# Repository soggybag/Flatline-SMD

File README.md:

# Flatline+ (1590B)

An optical compressor for guitar, built on John Hollis's Flatline with Atomium Amps' mods and your OPA2134 build (super-freq.com/flatline-op2134). Added:
- BLEND (parallel compression);
- a gain-reduction LED;
- a RELEASE switch;
- a side chain buffered off the audio path.

SMD parts are assembled by JLCPCB; the panel parts are hand-soldered on the back.

## Controls

| Control | Part | What it does |
|---|---|---|
| SUSTAIN | RV1 A100k | Gain into the optical gain cell (×3 to ×23): more sustain, more squash |
| BLEND | RV3 B100k | Dry ↔ compressed |
| VOLUME | RV4 A100k | Output level |
| RELEASE | SW1 sub-mini SPDT | FAST 220 µF (stock) / SLOW 440 µF |
| GR LED | D6 | Glows as hard as it's compressing |
| ON LED | D7 | Lit by the footswitch (LED_K) |
| Trim | RV2 3362P 1k | LED-string current (the original POT1) |

## Board

- **Outline and drilling:** the Trem v2 board outline (45 × 50 mm) and its 1590B panel grid.
  - Top row: SUSTAIN · GR LED · VOLUME.
  - Middle: RELEASE · BLEND · ON LED.
  - Bottom: footswitch.
- **Wiring:** a 1×4 header (IN / LED / GND / OUT) runs straight to SwitchPCB v2. There are 9V/GND pads, and IN GND / OUT GND pads for the jack sleeves.
- **Op-amps:** U1 OPA2134UA (LCSC C87361, extended) for audio; U2 TL072 (C6961) for the side chain.
- **Vactrol (U3):** Xvive VTL5C3, or a DIY LED + LDR in heat-shrink. It stands vertically between RELEASE and BLEND.
- **Release caps:** C8/C9 are 220 µF DMBJ (C970695), with `FT Rotation Offset 180` so JLC places them the right way round.

Design notes: [docs/Design Notes.md](docs/Design%20Notes.md). Schematic: [docs/Flatline_schematic.pdf](docs/Flatline_schematic.pdf).

## Status

- **2026-10-07:** schematic and board done.
  - ERC 0.
  - DRC 0 errors, 0 unconnected, schematic parity 0. Only silkscreen warnings remain.
  - GND pours on both layers.
- **Next:** your silkscreen pass, then the JLC fab files.

## Files

- `scripts/`:
  - `build_flatline.py`: the schematic;
  - `buildpcb_flatline.py`: placement;
  - `nudge.py`: clears overlaps.

  Don't re-run them after editing the board in KiCad.
- **Routing:** with `_tools/autoroute.py`.

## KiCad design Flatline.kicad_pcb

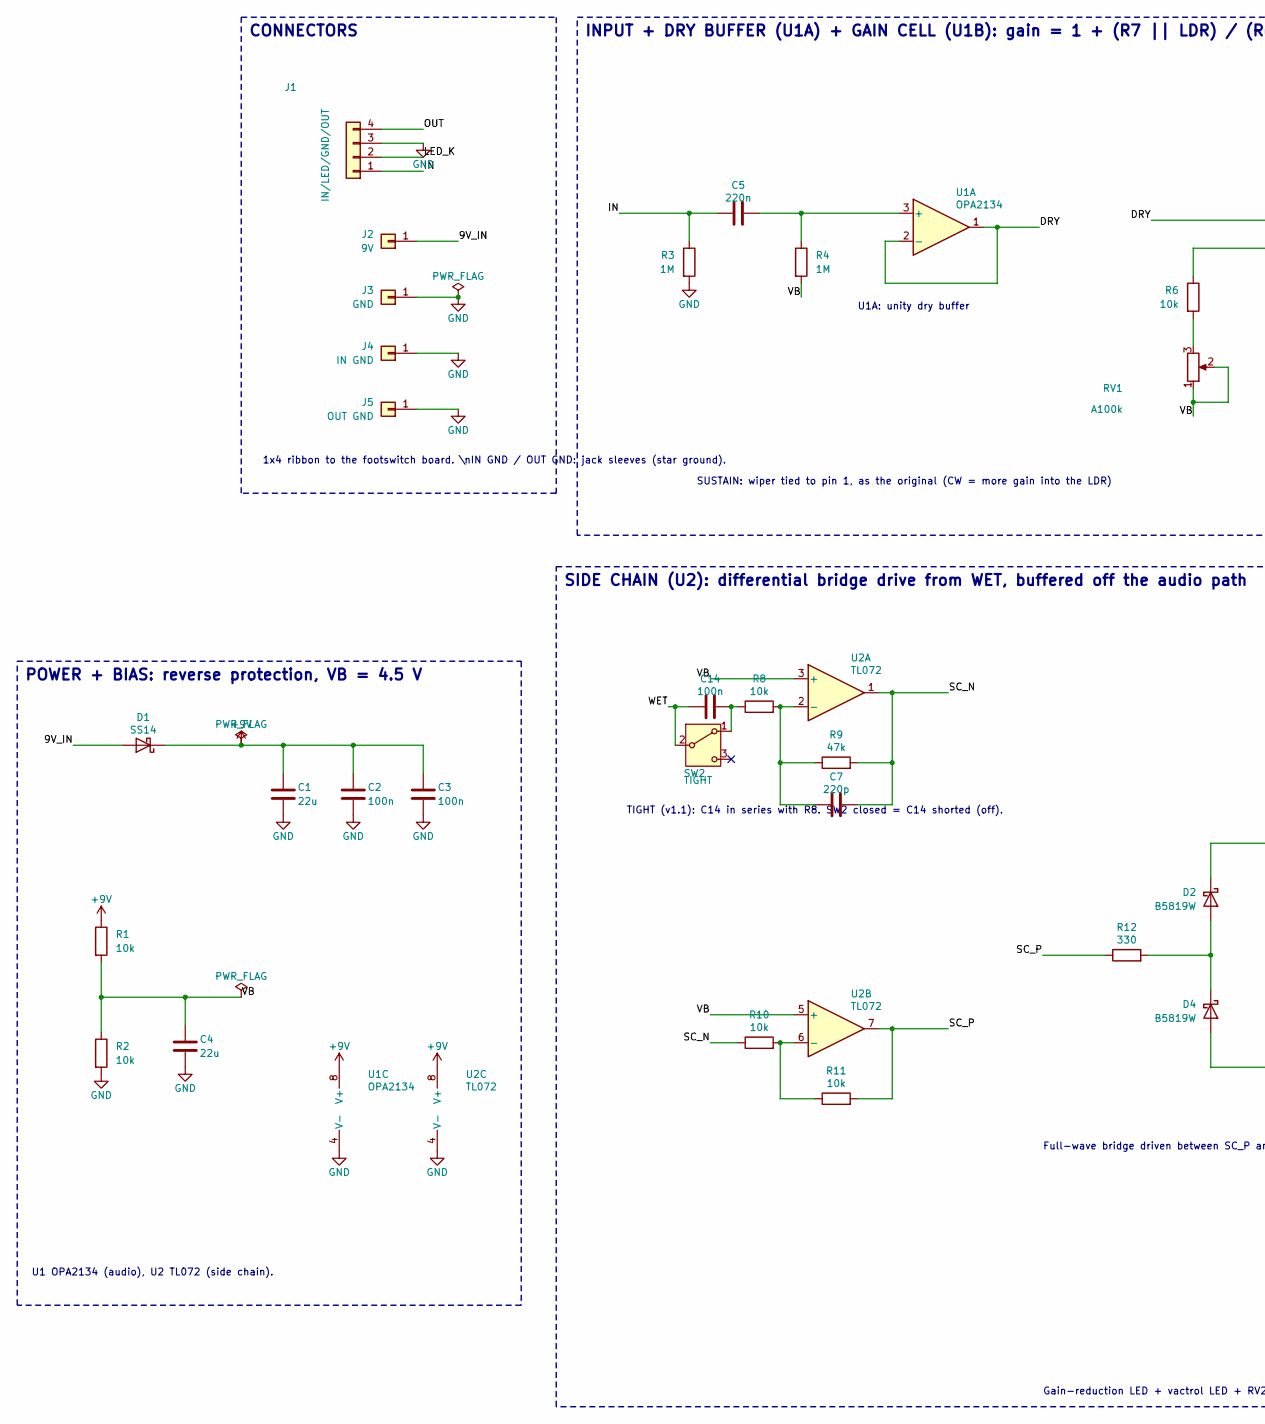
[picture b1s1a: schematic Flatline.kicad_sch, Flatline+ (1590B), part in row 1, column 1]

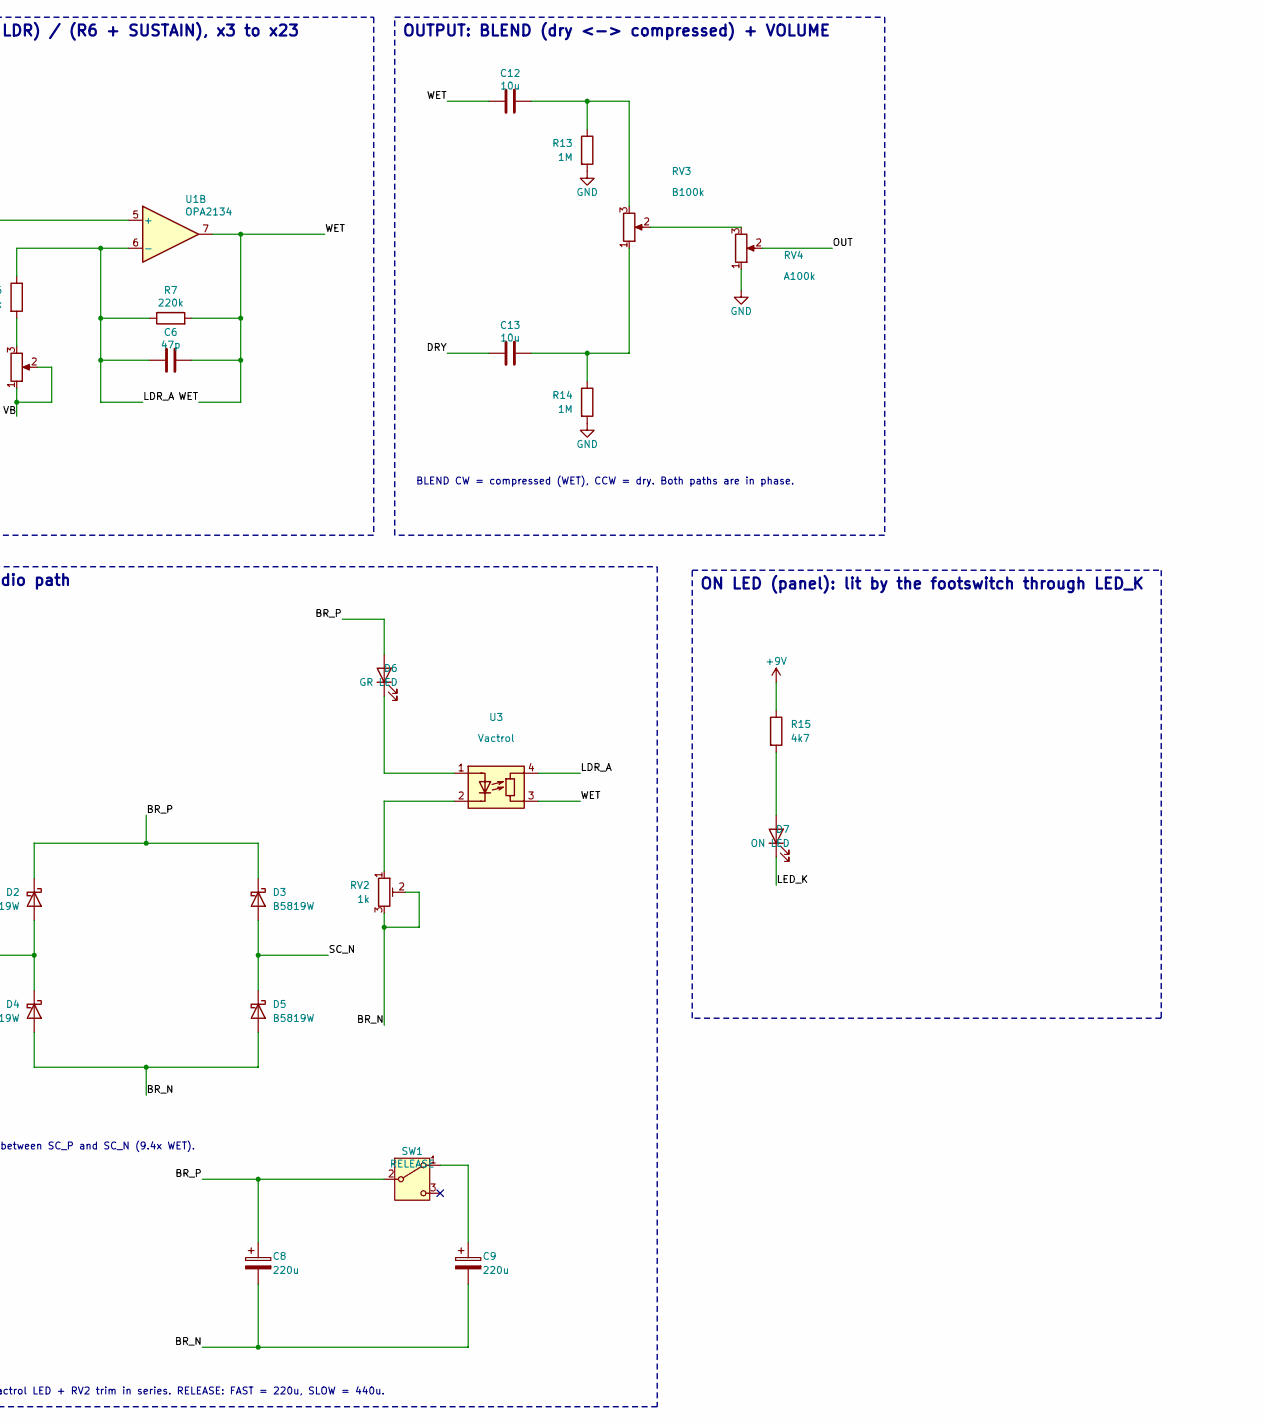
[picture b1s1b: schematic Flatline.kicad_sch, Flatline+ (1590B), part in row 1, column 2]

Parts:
C1, C4: 22u; C_0805_2012Metric_Pad1.18x1.45mm_HandSolder; LCSC C45783
C2, C3, C14: 100n; C_0805_2012Metric_Pad1.18x1.45mm_HandSolder; LCSC C49678
C5: 220n; C_0805_2012Metric_Pad1.18x1.45mm_HandSolder; LCSC C5378
C6: 47p; C_0805_2012Metric_Pad1.18x1.45mm_HandSolder; LCSC C14857
C7: 220p; C_0805_2012Metric_Pad1.18x1.45mm_HandSolder; LCSC C107145
C8, C9: 220u; CP_Elec_6.3x7.7; LCSC C970695
C12, C13: 10u; C_0805_2012Metric_Pad1.18x1.45mm_HandSolder; LCSC C15850
D1: SS14; D_SMA; LCSC C2480
D2, D3, D4, D5: B5819W; D_SOD-123; LCSC C8598
D6: GR LED; LED_D3.0mm
D7: ON LED; LED_D3.0mm
J1: IN/LED/GND/OUT; PinHeader_1x04_P2.54mm_Vertical
J2: 9V; SolderWire-0.5sqmm_1x01_D0.9mm_OD2.1mm
J3: GND; SolderWire-0.5sqmm_1x01_D0.9mm_OD2.1mm
J4: IN GND; SolderWire-0.5sqmm_1x01_D0.9mm_OD2.1mm
J5: OUT GND; SolderWire-0.5sqmm_1x01_D0.9mm_OD2.1mm
R1, R2, R6, R8, R10, R11: 10k; R_0805_2012Metric_Pad1.20x1.40mm_HandSolder; LCSC C17414
R3, R4, R13, R14: 1M; R_0805_2012Metric_Pad1.20x1.40mm_HandSolder; LCSC C17514
R7: 220k; R_0805_2012Metric_Pad1.20x1.40mm_HandSolder; LCSC C17556
R9: 47k; R_0805_2012Metric_Pad1.20x1.40mm_HandSolder; LCSC C17713
R12: 330; R_0805_2012Metric_Pad1.20x1.40mm_HandSolder; LCSC C17630
R15: 4k7; R_0805_2012Metric_Pad1.20x1.40mm_HandSolder; LCSC C17673
RV1, RV4: A100k; Potentiometer_Alpha_RD901F-40-00D_Single_Vertical
RV2: 1k; Potentiometer_Bourns_3362P_Vertical
RV3: B100k; Potentiometer_Alpha_RD901F-40-00D_Single_Vertical
SW1: RELEASE; SW_Taiway_200_SPDT
SW2: TIGHT; SW_Taiway_200_SPDT
U1: OPA2134; SOIC-8_3.9x4.9mm_P1.27mm; LCSC C87361
U2: TL072; SOIC-8_3.9x4.9mm_P1.27mm; LCSC C6961
U3: Vactrol; Vactrol_LED_LDR_DIY

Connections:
/9V_IN: D1.2 (A), J2.1
/BR_N: C8.2, C9.2, D4.2 (A), D5.2 (A), RV2.2, RV2.3
/BR_P: C8.1, D2.1 (K), D3.1 (K), D6.2 (A), SW1.2 (B)
/DRY: C13.1, U1.1, U1.2 (-), U1.5 (+)
/IN: C5.1, J1.1, R3.1
/LDR_A: C6.1, R6.1, R7.1, U1.6 (-), U3.4 (R)
/LED_K: D7.1 (K), J1.2
/OUT: J1.4, RV4.2
/SC_N: C7.2, D3.2 (A), D5.1 (K), R9.2, R10.1, U2.1
/SC_P: R11.2, R12.1, U2.7
/WET: C6.2, C12.1, C14.1, R7.2, SW2.2 (B), U1.7, U3.3 (R)
unnamed: C12.2, R13.1, RV3.3
unnamed: C13.2, R14.1, RV3.1
unnamed: D2.2 (A), D4.1 (K), R12.2
unnamed: D6.1 (K), U3.1 (A)
unnamed: D7.2 (A), R15.2
unnamed: R6.2, RV1.3
unnamed: RV3.2, RV4.3
unnamed: C9.1, SW1.1 (A)
unnamed: C14.2, R8.1, SW2.1 (A)
unnamed: C5.2, R4.1, U1.3 (+)
unnamed: C7.1, R8.2, R9.1, U2.2 (-)
unnamed: R10.2, R11.1, U2.6 (-)
unnamed: RV2.1, U3.2 (K)

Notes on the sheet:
Full-wave bridge driven between SC_P and SC_N (9.4x WET).
BLEND CW = compressed (WET), CCW = dry. Both paths are in phase.
INPUT + DRY BUFFER (U1A) + GAIN CELL (U1B): gain = 1 + (R7 || LDR) / (R6 + SUSTAIN), x3 to x23
U1A: unity dry buffer
ON LED (panel): lit by the footswitch through LED_K
SIDE CHAIN (U2): differential bridge drive from WET, buffered off the audio path
POWER + BIAS: reverse protection, VB = 4.5 V
1x4 ribbon to the footswitch board. \nIN GND / OUT GND: jack sleeves (star ground).
U1 OPA2134 (audio), U2 TL072 (side chain).
Gain-reduction LED + vactrol LED + RV2 trim in series. RELEASE: FAST = 220u, SLOW = 440u.
SUSTAIN: wiper tied to pin 1, as the original (CW = more gain into the LDR)
CONNECTORS
OUTPUT: BLEND (dry <-> compressed) + VOLUME
TIGHT (v1.1): C14 in series with R8. SW2 closed = C14 shorted (off).

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
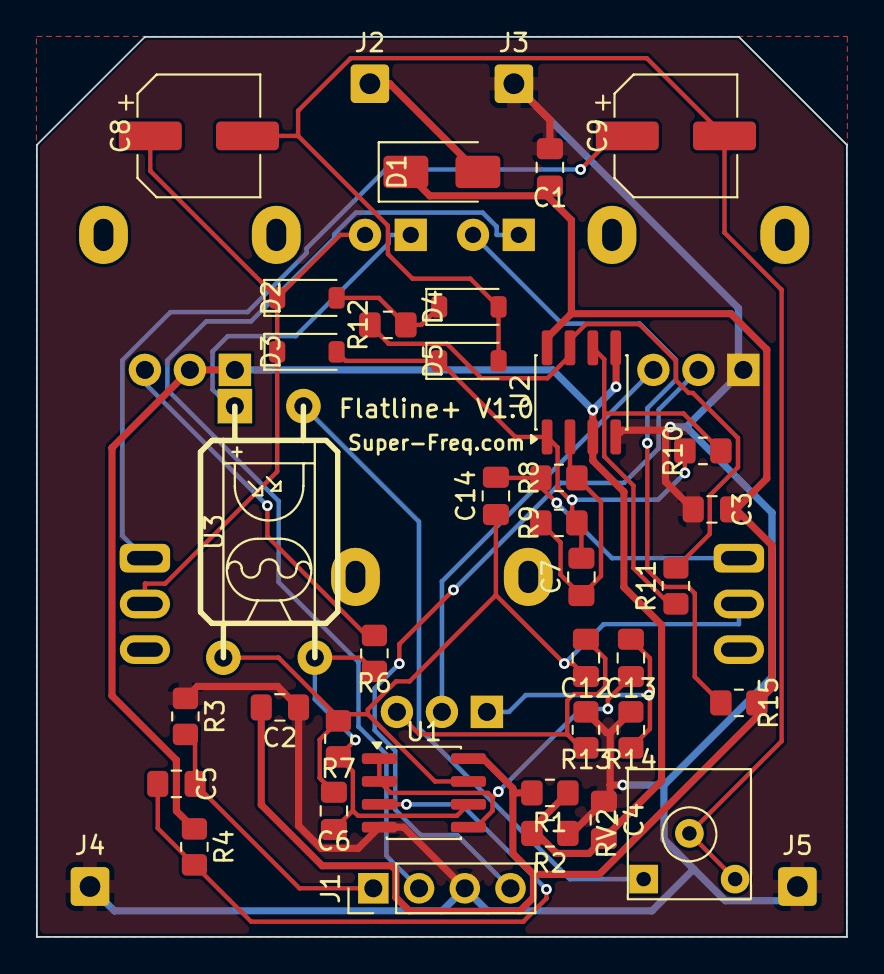
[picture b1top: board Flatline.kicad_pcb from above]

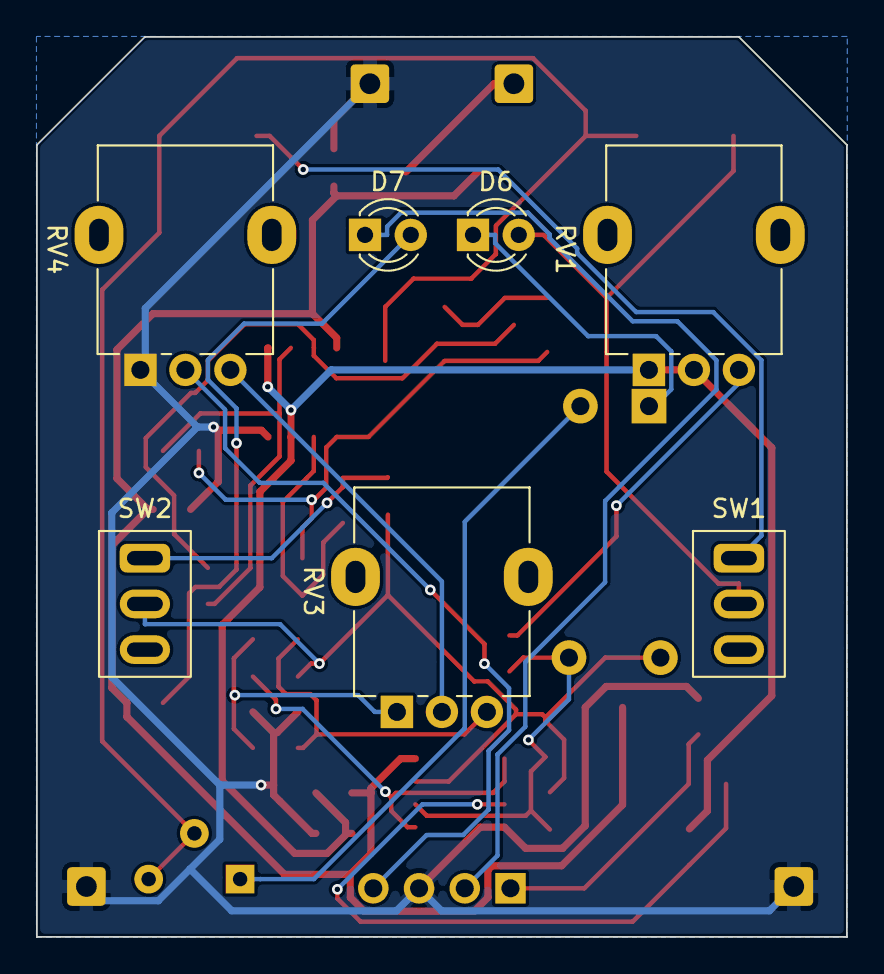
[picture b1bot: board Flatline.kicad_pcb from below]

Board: 2 copper layers, 45.0 x 50.0 mm, 48 parts (8 on the bottom side), 27 nets.

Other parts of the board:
ENC1: Hammond 1590B; Hammond_1590B
